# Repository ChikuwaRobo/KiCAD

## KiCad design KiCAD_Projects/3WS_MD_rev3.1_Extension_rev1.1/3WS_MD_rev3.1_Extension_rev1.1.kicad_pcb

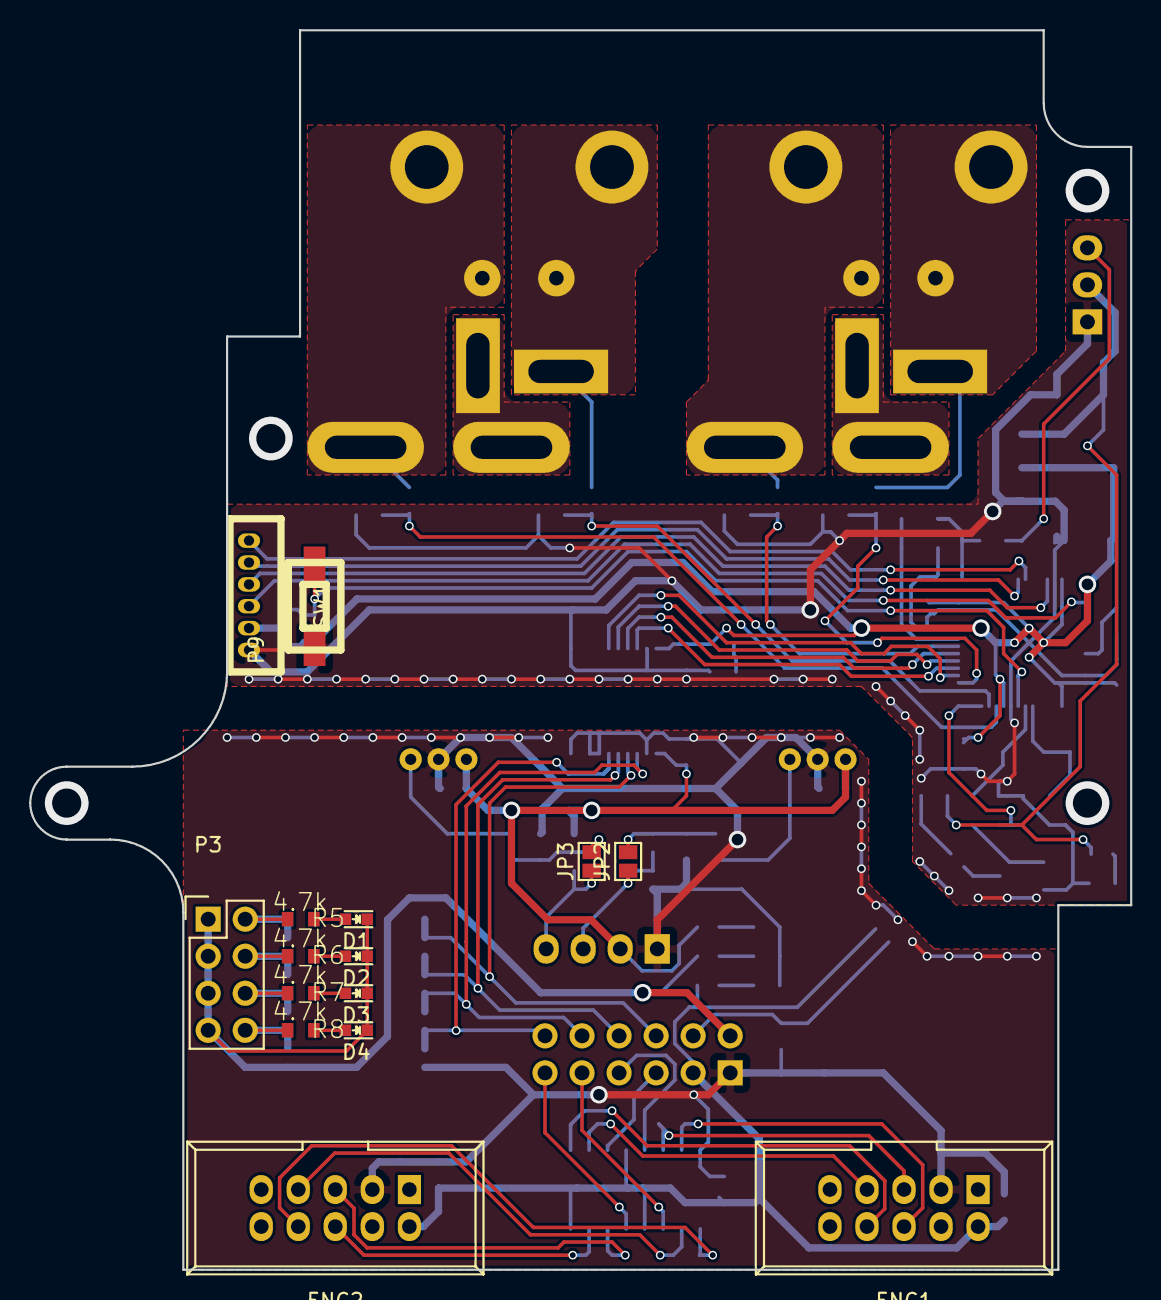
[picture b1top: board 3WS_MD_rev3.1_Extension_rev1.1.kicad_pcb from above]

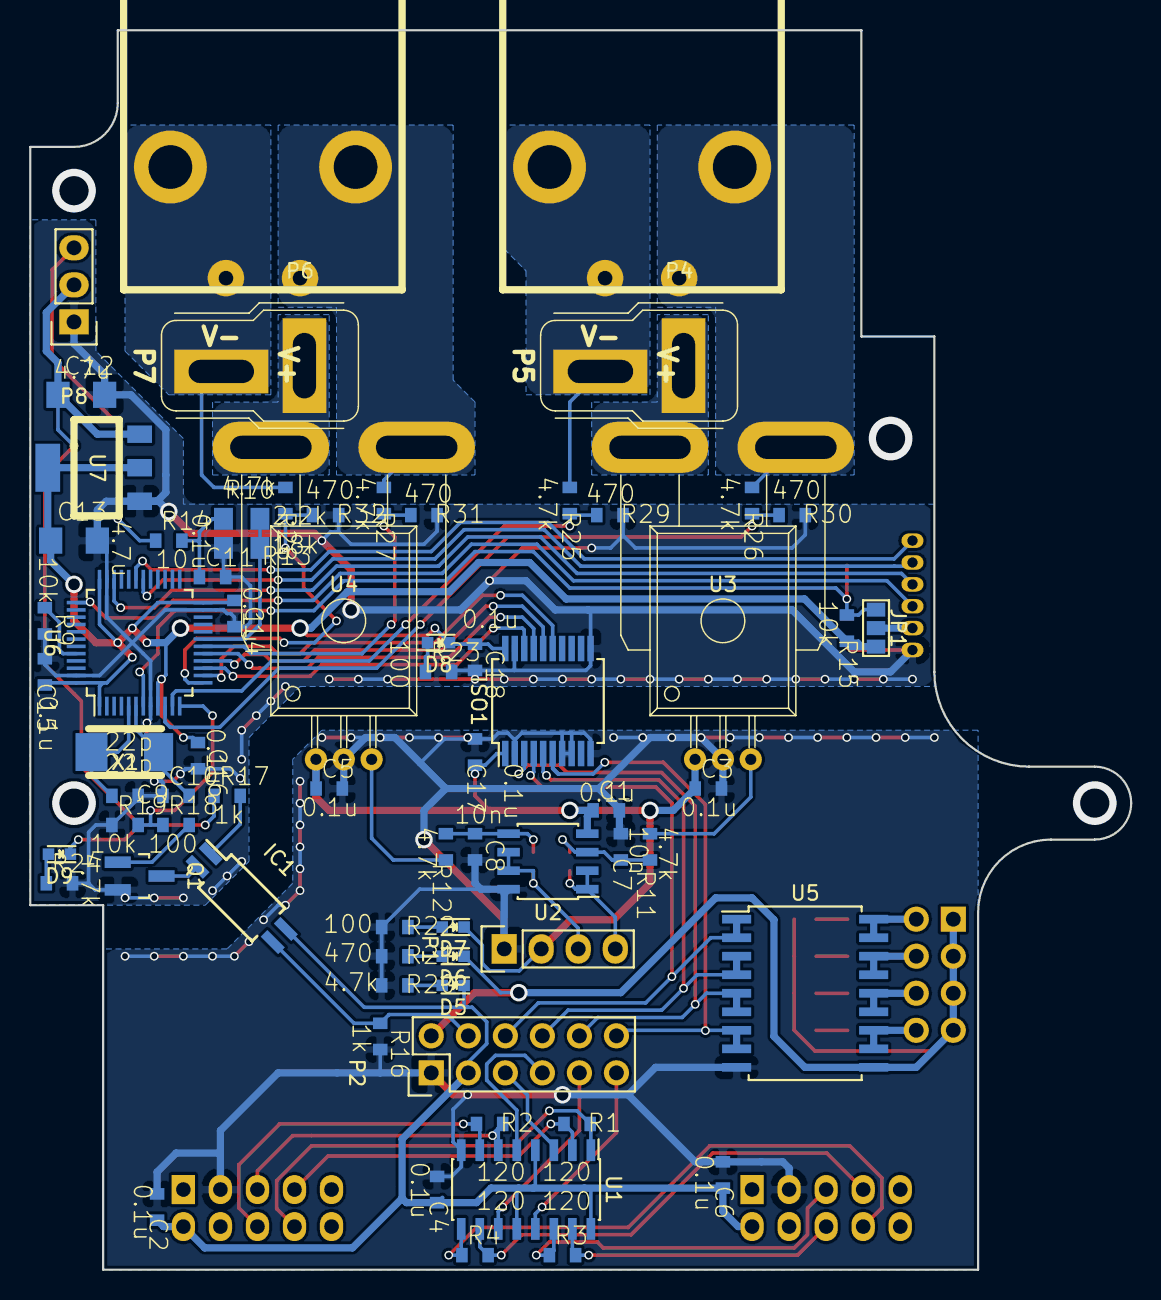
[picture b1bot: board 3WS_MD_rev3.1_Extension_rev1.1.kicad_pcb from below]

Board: 2 copper layers, 75.5 x 85.0 mm, 85 parts (70 on the bottom side), 73 nets.

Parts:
C1, C2, C3, C4, C5, C6, C11, C14, C15, C16, C17, C18: 0.1u; C1608_WP
C7, C8: 10n; C1608_WP
C9, C10: 22p; C1608_WP
C12, C13: 4.7u; C3216
D1, D2, D3, D4, D5, D6, D7, D8, D9: LED; LED_0603
ENC1, ENC2: RS422_ENCODER; DEF_ENCODER
IC1: TLP291; SOIJ-4_5.3x5.3mm_Pitch1.27mm
ISO1: ADuM3154; SSOP-20_5.3x7.2mm_Pitch0.65mm
JP1: JUMPER3; GS3
JP2, JP3: JUMPER; GS2
P1: CONN_01X04; Pin_Header_Straight_1x04
P2: CONN_02X06; Pin_Header_Straight_2x06
P3: CONN_02X04; Pin_Header_Straight_2x04
P4, P6: CONN_01X02; D-3200S_2L_PW
P5, P7: CONN_01X02; DEANS_T_M
P8: CONN_01X03; Pin_Header_Straight_1x03
P9: CONN_01X06; ZH_6T
Q1: MOSFET_N; SOT-23_Handsoldering
R1, R2, R3, R4: 120; C1608_WP
R5, R6, R7, R8, R11, R12, R20, R24, R25, R26, R27, R28: 4.7k; C1608_WP
R9, R15, R19: 10k; C1608_WP
R10: 18k; C2012
R13: 2.2k; C2012
R14: 10; C1608_WP
R16, R17: 1k; C1608_WP
R18, R22, R23: 100; C1608_WP
R21, R29, R30, R31, R32: 470; C1608_WP
SW1: SW_PUSH; RP_SMD_Button
U1: SN75175; SOIC-16_3.9x9.9mm_Pitch1.27mm
U2: LM358; SOIC-8_3.9x4.9mm_Pitch1.27mm
U3, U4: ACS758; ACS785xCB
U5: TBD62083A; SOIC-18_7.5x11.6mm_Pitch1.27mm
U6: STM32F103_48; LQFP-48_7x7mm_Pitch0.5mm
U7: NCP1117ST33T3G; SOT-223_reg
X1: CRYSTAL; ABM3_2pads

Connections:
+3.3V: C1.1, C3.1, C5.1, C17.1, D7.1, ISO1.1, P1.2, U2.4, U3.1, U4.1
+5V: C2.1, C4.1, C6.1, D5.1, ENC1.2, ENC2.2, IC1.4, P2.3, U1.4, U1.12, U1.16
+12V: D1.1, D2.1, D3.1, D4.1, D6.1, P2.2, P3.1, P3.3, P3.5, P3.7, U5.10
+BATT: P8.3, R14.1
/BATT_IN: R10.2, R13.1, U6.19
/ENC_Aa: P2.5, U1.3
/ENC_Aaa: ENC1.7, R1.2, U1.2
/ENC_Aab: ENC1.8, R1.1, U1.1
/ENC_Ab: P2.7, U1.5
/ENC_Aba: ENC1.5, R2.1, U1.6
/ENC_Abb: ENC1.6, R2.2, U1.7
/ENC_Ba: P2.9, U1.11
/ENC_Baa: ENC2.7, R4.2, U1.10
/ENC_Bab: ENC2.8, R4.1, U1.9
/ENC_Bb: P2.11, U1.13
/ENC_Bba: ENC2.5, R3.1, U1.14
/ENC_Bbb: ENC2.6, R3.2, U1.15
/EXIO_0: JP2.1, P1.3, U2.6, U2.7
/EXIO_1: JP3.1, P1.4, U2.1, U2.2
/GD_12V: C12.1, D9.1, P8.2, R17.1, U7.3
/NRST: JP1.1, R15.2, SW1.1, U6.7
/OUT_0: P3.2, R5.2, U5.17, U5.18
/OUT_1: P3.4, R6.2, U5.15, U5.16
/OUT_2: P3.6, R7.2, U5.13, U5.14
/OUT_3: P3.8, R8.2, U5.11, U5.12
/PW_3.3V: C13.1, C14.1, C15.1, C16.1, C18.1, D8.1, ISO1.20, JP1.3, R15.1, U6.1, U6.9, U6.24, U6.36, U6.48, U7.2
/SPI_MISO: ISO1.16, U6.16
/SPI_MOSI: ISO1.17, U6.17
/SPI_NSS: ISO1.15, U6.14
/SPI_SCK: ISO1.18, U6.15
/SWDCK: P9.3, U6.37
/SWDIO: P9.4, U6.34
/USART_RX: P9.6, U6.31
/USART_TX: P9.5, U6.30
/V0A_IN: R27.1, R31.2, U6.18
/V0B_IN: R28.1, R32.2, U6.13
/V1A_IN: R26.1, R30.2, U6.10
/V1B_IN: R25.1, R29.2, U6.11
/VALVE_0: ISO1.6, P2.12, U5.7, U5.8
/VALVE_1: ISO1.3, P2.10, U5.5, U5.6
/VALVE_2: ISO1.5, P2.8, U5.3, U5.4
/VALVE_3: ISO1.4, P2.6, U5.1, U5.2
/V_0A: P6.1, R27.2, U4.4
/V_0B: P6.2, P7.2, R28.2
/V_1A: P4.1, R26.2, U3.4
/V_1B: P4.2, P5.2, R25.2
/V_RX: IC1.3, P2.4, R16.1
/V_TX: R18.1, R19.2, U6.12
GND: C1.2, C2.2, C3.2, C4.2, C5.2, C6.2, C7.2, C8.2, C17.2, ENC1.3, ENC2.3, ISO1.2, ISO1.7, ISO1.8, ISO1.10, P1.1, P2.1, R16.2, R20.2, R21.2, R22.2, U1.8, U2.8, U3.2, U4.2, U5.9
GNDPWR: C9.1, C10.1, C11.2, C12.2, C13.2, C14.2, C15.2, C16.2, C18.2, ISO1.11, ISO1.19, P8.1, P9.1, Q1.S, R9.2, R13.2, R19.1, R23.2, R24.2, R29.1, R30.1, R31.1, R32.1, SW1.2, U6.8, U6.23, U6.35, U6.47, U7.1
unnamed: C7.1, JP3.2, R11.2, U2.3
unnamed: C8.1, JP2.2, R12.2, U2.5
unnamed: C9.2, U6.5, X1.1
unnamed: C10.2, U6.6, X1.2
unnamed: C11.1, R10.1, R14.2
unnamed: D1.2, R5.1
unnamed: D2.2, R6.1
unnamed: D3.2, R7.1
unnamed: D4.2, R8.1
unnamed: D5.2, R20.1
unnamed: D6.2, R21.1
unnamed: D7.2, R22.1
unnamed: D8.2, R23.1
unnamed: D9.2, R24.1
unnamed: IC1.1, R17.2
unnamed: IC1.2, Q1.D
unnamed: JP1.2, P9.2
unnamed: P5.1, U3.5
unnamed: P7.1, U4.5
unnamed: Q1.G, R18.2
unnamed: R9.1, U6.44
unnamed: R11.1, U3.3
unnamed: R12.1, U4.3

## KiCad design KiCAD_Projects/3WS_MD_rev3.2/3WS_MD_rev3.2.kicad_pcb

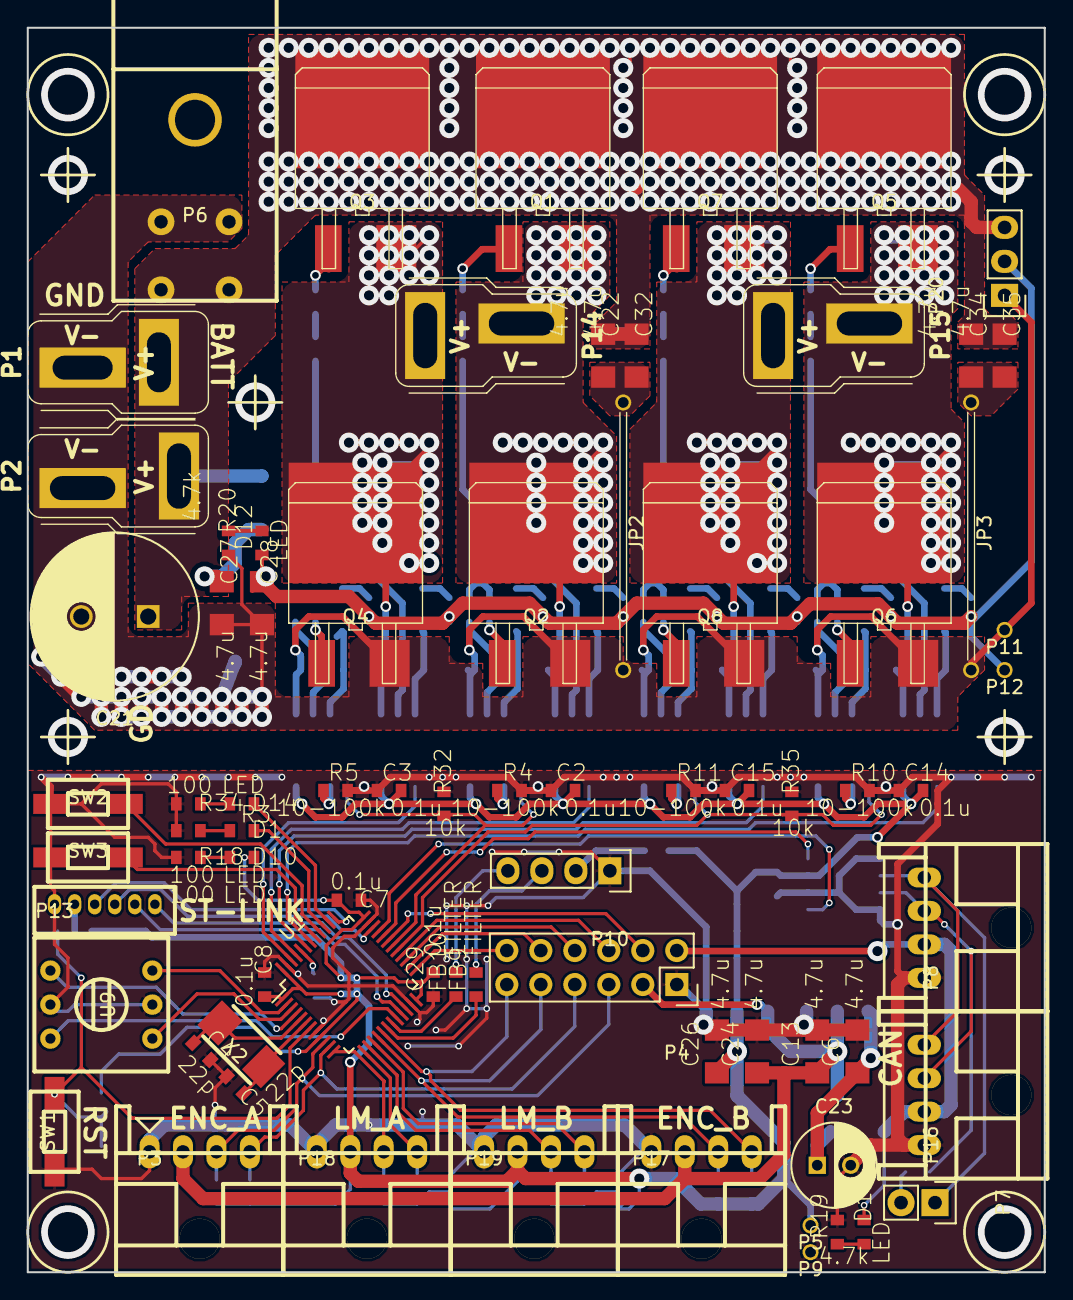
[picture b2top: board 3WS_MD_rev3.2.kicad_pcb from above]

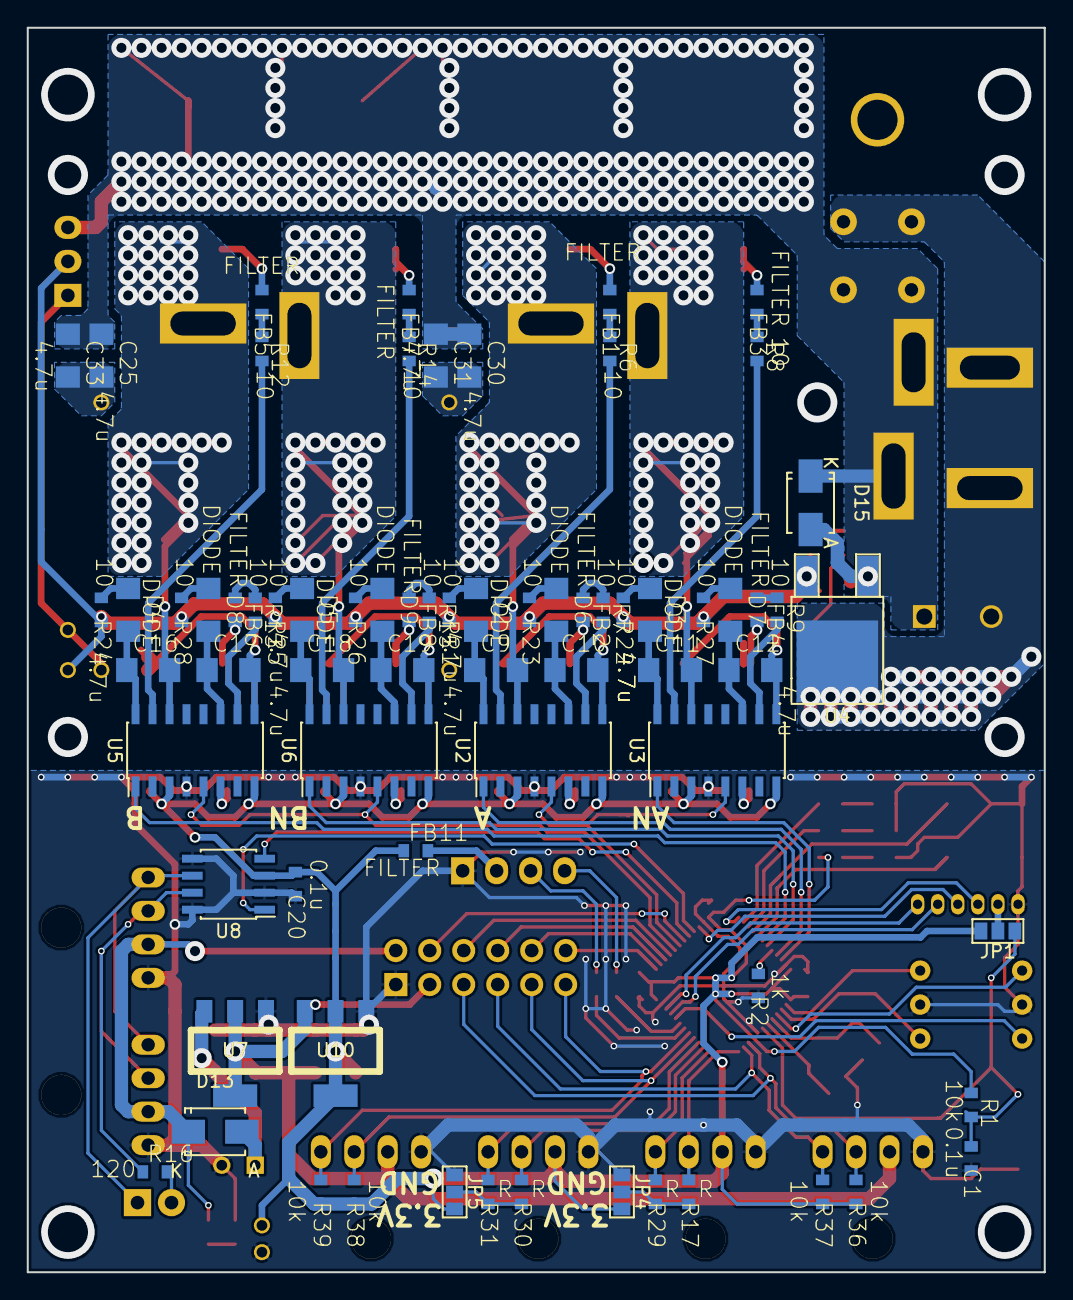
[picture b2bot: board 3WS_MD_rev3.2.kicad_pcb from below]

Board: 2 copper layers, 76.0 x 93.0 mm, 146 parts (71 on the bottom side), 112 nets.

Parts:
C1, C2, C3, C7, C8, C14, C15, C20, C29: 0.1u; C1608_WP
C4, C5: 22p; C1608_WP
C6, C9, C10, C11, C12, C13, C16, C17, C18, C19, C22, C24, C25, C26, C27, C28, C30, C31, C32, C33, C34, C35: 4.7u; C3216
C21: 470u; C_Radial_D12.5_L25_P5
C23: 100u; C_Radial_D6.3_L11.2_P2.5
D1, D10, D11, D12, D14: LED; C1608_WP
D2, D3, D4, D5, D6, D7, D8, D9: DIODE; C3216
D13, D15: DIODE; SMA_Standard
FB1, FB2, FB3, FB4, FB5, FB6, FB7, FB8, FB9, FB10, FB11: FILTER; C1608_WP
JP1, JP4, JP5: JUMPER3; GS3
JP2, JP3: JUMPER; 20mmJumper
P1: CONN_01X02; DEANS_T_M
P2, P14, P15: CONN_01X02; DEANS_T_F
P3, P8, P16, P17, P18, P19: CONN_01X04; XA_4LC
P4: CONN_02X06; Socket_Strip_Straight_2x06
P5, P9, P11, P12: TST; testPin
P6: CONN_01X04; D-3500D_4S
P7: CONN_01X02; Pin_Header_Straight_1x02
P10: CONN_01X04; Socket_Strip_Straight_1x04
P13: CONN_01X06; ZH_6T
P20: CONN_01X03; Socket_Strip_Straight_1x03
Q1, Q2, Q3, Q4, Q5, Q6, Q7, Q8: MOSFET_N; D2-PAK_compact
R1, R32, R35, R36, R37, R38, R39: 10k; C1608_WP
R2: 1k; C1608_WP
R3, R18, R34: 100; C1608_WP
R4, R5, R10, R11: 10-100k; C1608_WP
R6, R7, R8, R9, R12, R13, R14, R15, R21, R22, R23, R24, R25, R26, R27, R28: 10; C1608_WP
R16: 120; C1608_WP
R17, R29, R30, R31: R; C1608_WP
R19, R20: 4.7k; C1608_WP
SW1, SW2, SW3: SW_PUSH; RP_SMD_Button
U1: STM32F103_48; LQFP-48_7x7mm_Pitch0.5mm
U2, U3, U5, U6: SI8234; SOIC-16_3.9x9.9mm_Pitch1.27mm
U4: LM7812; TO-252-2Lead_regu
U7, U10: NCP1117ST33T3G; SOT-223_reg
U8: MAX3051; SOIC-8_3.9x4.9mm_Pitch1.27mm
U9: SW_ROTARY_16; rotary_0F
X2: CRYSTAL; ABM3_2pads

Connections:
+3.3V: C2.2, C3.2, C7.2, C8.2, C14.2, C15.2, C20.2, C26.1, C29.2, D10.1, FB11.1, JP1.3, JP4.3, JP5.3, P5.1, P18.2, P19.2, R1.1, R36.1, R37.1, R38.1, R39.1, U1.1, U1.9, U1.24, U1.36, U1.48, U2.3, U2.8, U3.3, U3.8, U5.3, U5.8, U6.3, U6.8, U8.3, U10.2
+5V: C13.1, C24.1, P3.2, P4.3, P17.2, U7.2, U10.3
+12V: D11.1, D13.1, P4.2, P8.2, P16.2
+BATT: C21.1, C22.1, C25.1, C30.1, C31.1, C32.1, C33.1, C34.1, C35.1, D15.1, P1.1, P2.1, P6.2, P6.4, P20.3, Q1.D, Q3.D, Q5.D, Q7.D
/BOOT0: R2.2, U1.44
/CANH: P8.3, P16.3, R16.1, U8.7
/CANL: P7.1, P8.4, P16.4, U8.6
/CAN_RX: U1.32, U8.4
/CAN_TX: U1.33, U8.1
/ENC_Aa: P3.3, P4.5, R36.2, U1.10
/ENC_Ab: P3.4, P4.7, R37.2, U1.11
/ENC_Ba: P4.9, P17.3, R38.2, U1.16
/ENC_Bb: P4.11, P17.4, R39.2, U1.17
/EXIO_0: FB9.2, P10.3
/EXIO_1: FB10.2, P10.4
/GD_12V: C28.1, D12.1, P12.1, P20.2, R21.1, R22.1, R23.1, R24.1, R25.1, R26.1, R27.1, R28.1, U4.VO
/LED_A: D14.1, U1.38
/LED_B: D1.1, U1.39
/LIMIT_A1: P18.3, R17.2, U1.12
/LIMIT_A2: P18.4, R29.2, U1.13
/LIMIT_B1: P19.3, R30.2, U1.14
/LIMIT_B2: P19.4, R31.2, U1.15
/MOTORA_EN: R32.2, U1.30, U2.5, U3.5
/MOTORB_EN: R35.2, U1.29, U5.5, U6.5
/NRST: C1.2, JP1.1, R1.2, SW1.2, U1.7
/OSC_IN: C4.1, U1.5, X2.1
/OSC_OUT: C5.1, U1.6, X2.2
/OUT_A: C9.2, P14.2, Q1.S, Q2.D, U2.14
/OUT_AN: C11.2, P14.1, Q3.S, Q4.D, U3.14
/OUT_B: C16.2, P15.2, Q5.S, Q6.D, U5.14
/OUT_BN: C18.2, P15.1, Q7.S, Q8.D, U6.14
/PWM_A: U1.45, U2.1
/PWM_AN: U1.46, U3.1
/PWM_B: U1.42, U5.1
/PWM_BN: U1.43, U6.1
/SEL_1: U1.2, U9.3
/SEL_2: U1.3, U9.1
/SEL_4: U1.4, U9.4
/SEL_8: U1.20, U9.6
/SW1: SW2.2, U1.40
/SW2: SW3.2, U1.41
/SWCLK: P13.3, U1.37
/SWDIO: P13.4, U1.34
/USART_RX: P13.6, U1.22
/USART_TX: P13.5, U1.21
/VALVE_0: P4.12, U1.25
/VALVE_1: P4.10, U1.26
/VALVE_2: P4.8, U1.27
/VALVE_3: P4.6, U1.28
/V_RX: P4.4, U1.31
GND: C1.1, C2.1, C3.1, C4.2, C5.2, C6.2, C7.1, C8.1, C13.2, C14.1, C15.1, C20.1, C23.2, C24.2, C26.2, C29.1, JP4.1, JP5.1, P3.1, P4.1, P8.1, P9.1, P10.1, P13.1, P16.1, P17.1, P18.1, P19.1, R2.1, R3.2, R4.2, R5.2, R10.2, R11.2, R18.2, R19.2, R32.1, R34.2, R35.1, SW1.1, SW2.1, SW3.1, U1.8, U1.23, U1.35, U1.47, U2.4, U3.4, U5.4, U6.4, U7.1, U8.2, U8.5, U8.8, U9.2, U9.5, U10.1
GNDPWR: C10.2, C12.2, C17.2, C19.2, C21.2, C27.2, C28.2, JP2.1, JP3.1, P1.2, P2.2, P6.1, P6.3, P11.1, P20.1, Q2.S, Q4.S, Q6.S, Q8.S, R20.2, U2.9, U3.9, U4.GND, U5.9, U6.9
unnamed: C9.1, D2.2, U2.16
unnamed: C10.1, D6.2, U2.11
unnamed: C11.1, D3.2, U3.16
unnamed: C12.1, D7.2, U3.11
unnamed: C16.1, D4.2, U5.16
unnamed: C17.1, D8.2, U5.11
unnamed: C18.1, D5.2, U6.16
unnamed: C19.1, D9.2, U6.11
unnamed: C22.2, C30.2, C31.2, C32.2, JP2.2
unnamed: C6.1, C23.1, D13.2, U7.3
unnamed: C25.2, C33.2, C34.2, C35.2, JP3.2
unnamed: C27.1, D15.2, U4.VI
unnamed: D1.2, R3.1
unnamed: D2.1, R21.2
unnamed: D3.1, R22.2
unnamed: D4.1, R24.2
unnamed: D5.1, R25.2
unnamed: D6.1, R23.2
unnamed: D7.1, R27.2
unnamed: D8.1, R28.2
unnamed: D9.1, R26.2
unnamed: D10.2, R18.1
unnamed: D11.2, R19.1
unnamed: D12.2, R20.1
unnamed: D14.2, R34.1
unnamed: FB1.1, R6.1
unnamed: FB1.2, Q1.G
unnamed: FB2.1, R7.1
unnamed: FB2.2, Q2.G
unnamed: FB3.1, R8.1
unnamed: FB3.2, Q3.G
unnamed: FB4.1, R9.1
unnamed: FB4.2, Q4.G
unnamed: FB5.1, R12.1
unnamed: FB5.2, Q5.G
unnamed: FB6.1, R13.1
unnamed: FB6.2, Q6.G
unnamed: FB7.1, R14.1
unnamed: FB7.2, Q7.G
unnamed: FB8.1, R15.1
unnamed: FB8.2, Q8.G
unnamed: FB9.1, U1.18
unnamed: FB10.1, U1.19
unnamed: FB11.2, P10.2
unnamed: JP1.2, P13.2
unnamed: JP4.2, R17.1, R29.1
unnamed: JP5.2, R30.1, R31.1
unnamed: P7.2, R16.2
unnamed: R4.1, U2.6
unnamed: R5.1, U3.6
unnamed: R6.2, U2.15
unnamed: R7.2, U2.10
unnamed: R8.2, U3.15
unnamed: R9.2, U3.10
unnamed: R10.1, U5.6
unnamed: R11.1, U6.6
unnamed: R12.2, U5.15
unnamed: R13.2, U5.10
unnamed: R14.2, U6.15
unnamed: R15.2, U6.10

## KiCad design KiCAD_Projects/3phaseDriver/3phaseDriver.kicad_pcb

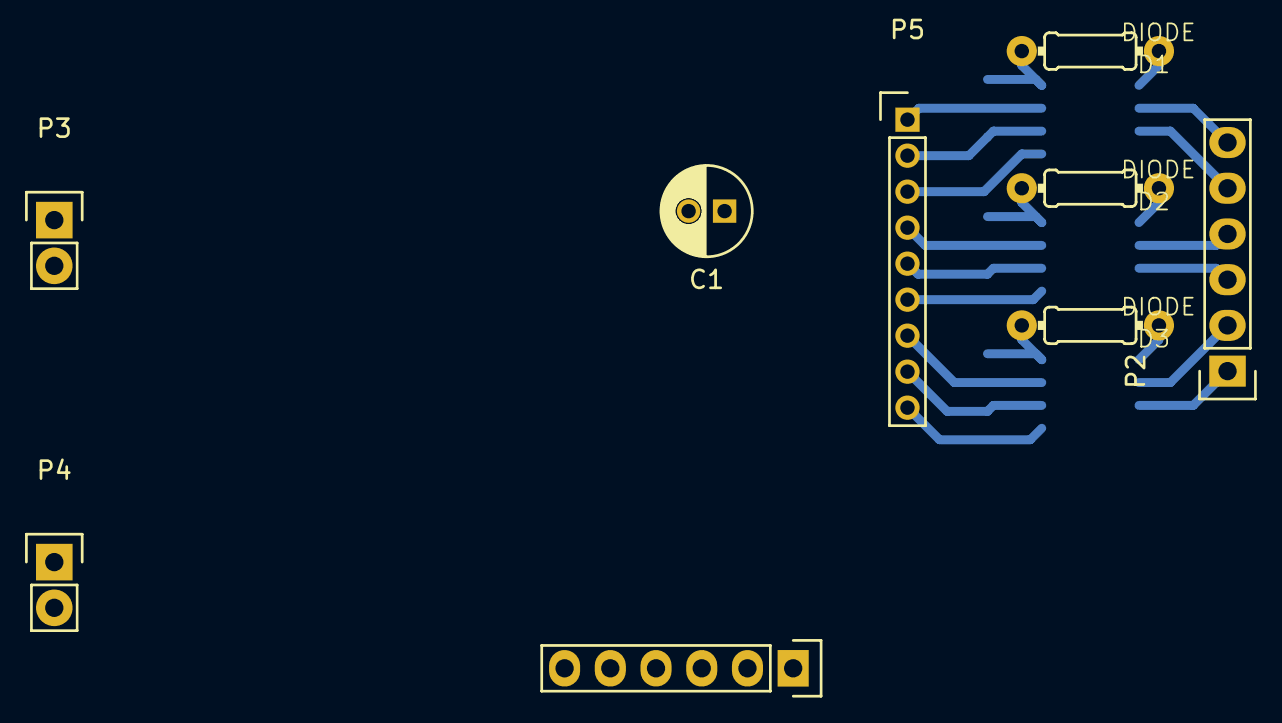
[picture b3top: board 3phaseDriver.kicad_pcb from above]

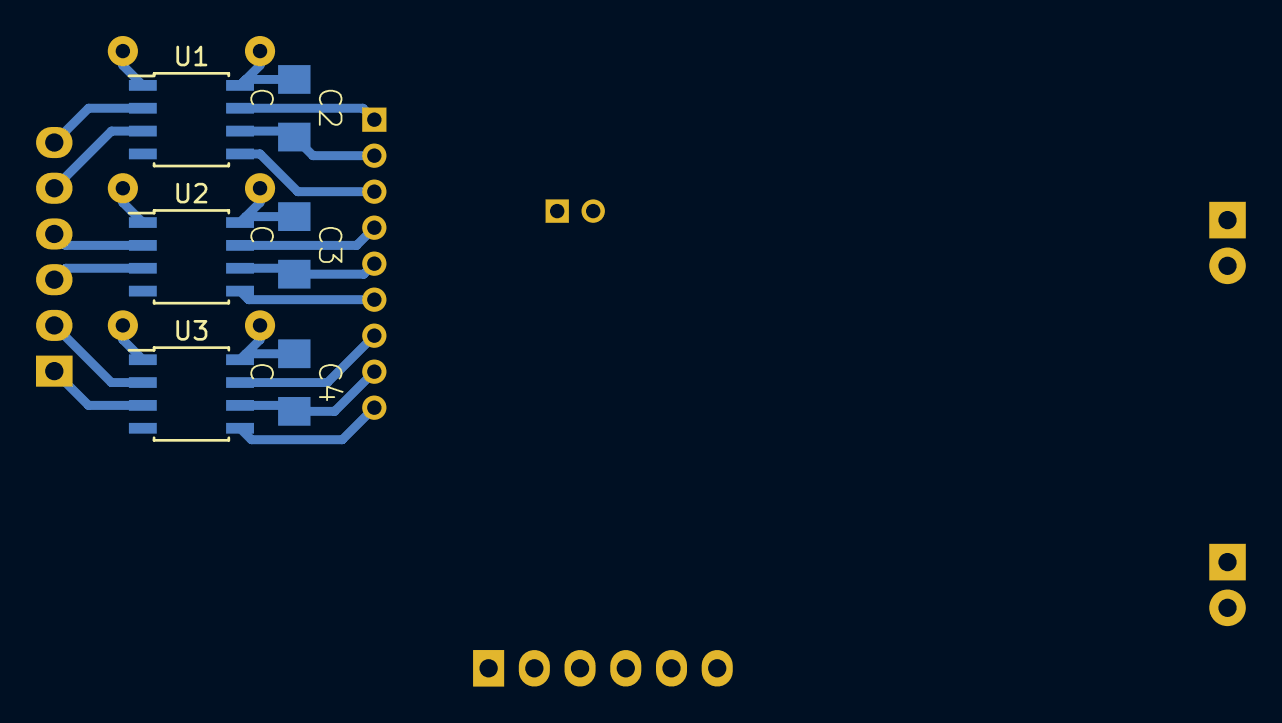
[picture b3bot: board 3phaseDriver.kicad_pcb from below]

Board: 2 copper layers, 15 parts (6 on the bottom side), 21 nets.

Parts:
C1: C; C_Radial_D5_L11_P2
C2, C3, C4: C; C3216
D1, D2, D3: DIODE; 0204_2f7
P1, P2: CONN_01X06; Socket_Strip_Straight_1x06
P3, P4: CONN_01X02; Pin_Header_Straight_1x02
P5: CONN_01X09; Pin_Header_Straight_1x09_Pitch2.00mm
U1, U2, U3: NCP5104; SOIC-8_3.9x4.9mm_Pitch1.27mm

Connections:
+12V: C1.1, D1.1, D2.1, D3.1, P1.3, P1.4, U1.1, U2.1, U3.1
+BATT: P1.5, P1.6, P3.1, P3.2
GND: C1.2, P1.1, P1.2, P4.1, P4.2, U1.4, U2.4, U3.4
unnamed: C2.1, D1.2, U1.8
unnamed: C2.2, P5.2, U1.6
unnamed: C3.1, D2.2, U2.8
unnamed: C3.2, P5.5, U2.6
unnamed: C4.1, D3.2, U3.8
unnamed: C4.2, P5.8, U3.6
unnamed: P2.1, U3.3
unnamed: P2.2, U3.2
unnamed: P2.3, U2.3
unnamed: P2.4, U2.2
unnamed: P2.5, U1.3
unnamed: P2.6, U1.2
unnamed: P5.1, U1.7
unnamed: P5.3, U1.5
unnamed: P5.4, U2.7
unnamed: P5.6, U2.5
unnamed: P5.7, U3.7
unnamed: P5.9, U3.5

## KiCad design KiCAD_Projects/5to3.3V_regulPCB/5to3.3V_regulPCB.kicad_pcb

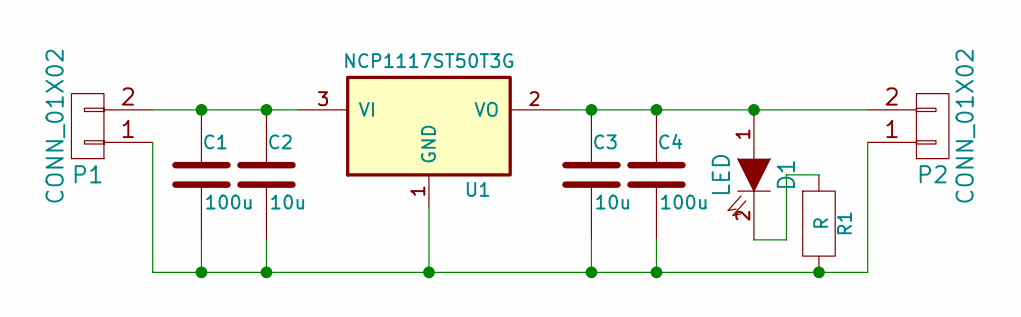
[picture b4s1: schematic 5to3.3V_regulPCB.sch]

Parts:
C1, C4: 100u; C_Radial_D6.3_L11.2_P2.5
C2, C3: 10u; C3216
D1: LED; LED-3MM
P1, P2: CONN_01X02; XA_2LC
R1: R; C1608_WP
U1: NCP1117ST50T3G; SOT-223_reg

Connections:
unnamed: C1.1, C2.1, P1.2, U1.3 (VI)
unnamed: C1.2, C2.2, C3.2, C4.2, P1.1, P2.1, R1.2, U1.1 (GND)
unnamed: C3.1, C4.1, D1.1 (A), P2.2, U1.2 (VO)
unnamed: D1.2 (K), R1.1

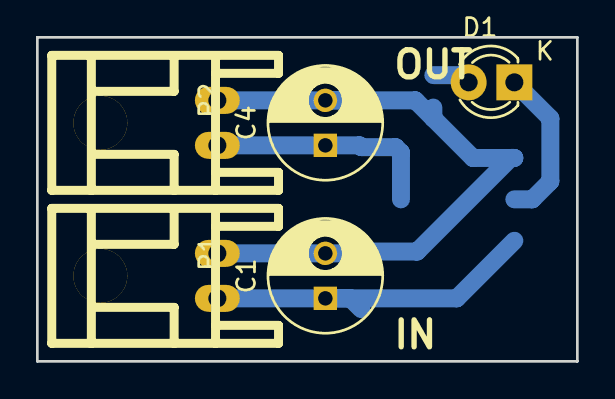
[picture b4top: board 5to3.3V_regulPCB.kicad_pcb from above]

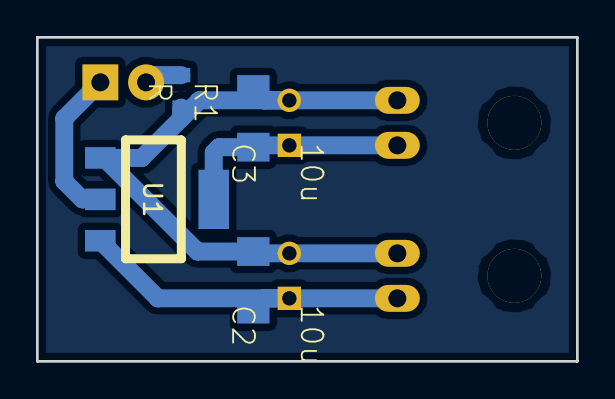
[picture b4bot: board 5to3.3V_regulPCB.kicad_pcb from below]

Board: 2 copper layers, 30.0 x 18.0 mm, 9 parts (4 on the bottom side), 4 nets.

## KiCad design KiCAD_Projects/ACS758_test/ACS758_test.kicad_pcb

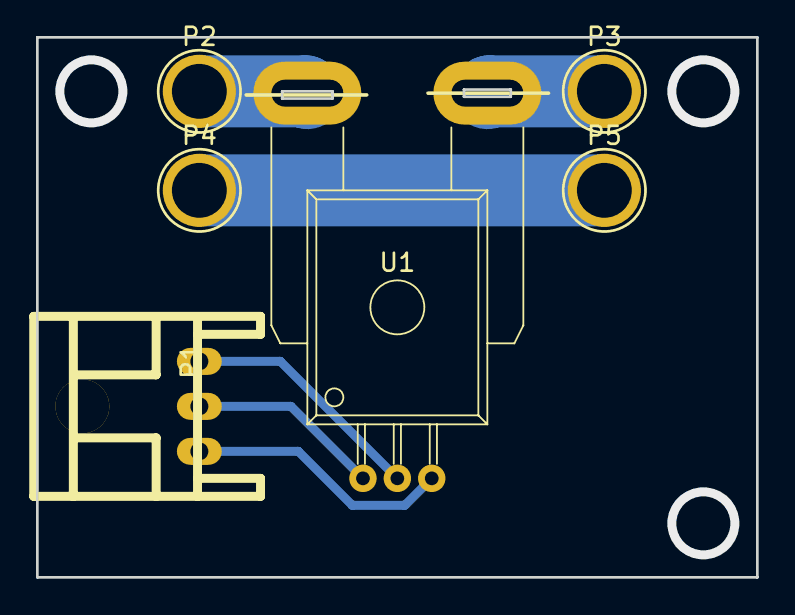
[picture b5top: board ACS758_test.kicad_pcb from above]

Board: 2 copper layers, 40.0 x 30.0 mm, 6 parts (0 on the bottom side), 6 nets.

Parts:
P1: CONN_01X03; XA_3LC
P2, P3, P4, P5: CONN_01X01; 1pin
U1: ACS758; ACS785xCB

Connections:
unnamed: P1.1, U1.2
unnamed: P1.2, U1.1
unnamed: P1.3, U1.3
unnamed: P2.1, U1.5
unnamed: P3.1, U1.4
unnamed: P4.1, P5.1
